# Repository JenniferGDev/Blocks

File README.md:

# Blocks
Modular Utility PCB System for breadboarding.

See the following thread where I introduced my personal breadboarding system:
https://www.modwiggler.com/forum/viewtopic.php?t=267893

The files provided here are in Kicad format.

The gerber files are available in gerber.zip.  They are setup for JLCPCB.

There is a "3D View.png" file in each module's folder, which is a screenshot of the PCB in Kicad's 3D Viewer.

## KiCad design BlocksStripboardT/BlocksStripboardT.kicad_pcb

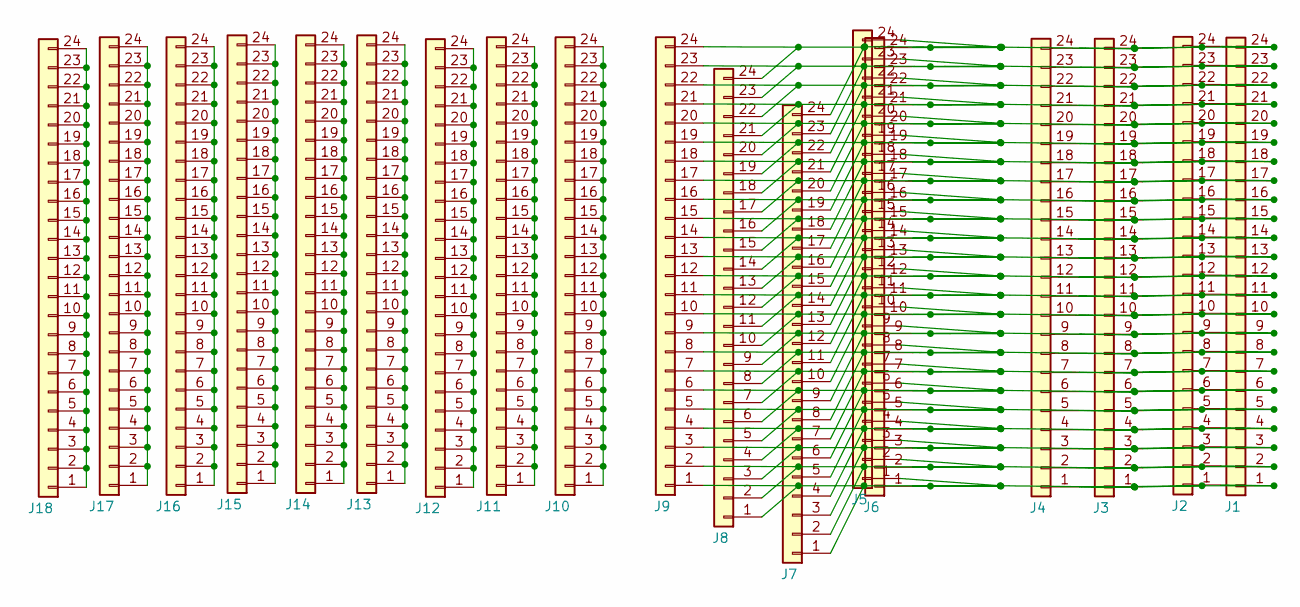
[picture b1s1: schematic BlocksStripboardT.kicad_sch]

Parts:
J1, J2, J3, J4, J5, J6, J7, J8, J9, J10, J11, J12, J13, J14, J15, J16, J17, J18: Conn_01x24; Stripboard_1x24_P2.54mm_Vertical

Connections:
unnamed: J1.1, J2.1, J3.1, J4.1, J5.1, J6.1, J7.1, J8.1, J9.1
unnamed: J1.2, J2.2, J3.2, J4.2, J5.2, J6.2, J7.2, J8.2, J9.2
unnamed: J1.3, J2.3, J3.3, J4.3, J5.3, J6.3, J7.3, J8.3, J9.3
unnamed: J1.5, J2.5, J3.5, J4.5, J5.5, J6.5, J7.5, J8.5, J9.5
unnamed: J1.4, J2.4, J3.4, J4.4, J5.4, J6.4, J7.4, J8.4, J9.4
unnamed: J1.6, J2.6, J3.6, J4.6, J5.6, J6.6, J7.6, J8.6, J9.6
unnamed: J1.7, J2.7, J3.7, J4.7, J5.7, J6.7, J7.7, J8.7, J9.7
unnamed: J1.8, J2.8, J3.8, J4.8, J5.8, J6.8, J7.8, J8.8, J9.8
unnamed: J1.9, J2.9, J3.9, J4.9, J5.9, J6.9, J7.9, J8.9, J9.9
unnamed: J1.10, J2.10, J3.10, J4.10, J5.10, J6.10, J7.10, J8.10, J9.10
unnamed: J1.11, J2.11, J3.11, J4.11, J5.11, J6.11, J7.11, J8.11, J9.11
unnamed: J1.12, J2.12, J3.12, J4.12, J5.12, J6.12, J7.12, J8.12, J9.12
unnamed: J1.13, J2.13, J3.13, J4.13, J5.13, J6.13, J7.13, J8.13, J9.13
unnamed: J1.14, J2.14, J3.14, J4.14, J5.14, J6.14, J7.14, J8.14, J9.14
unnamed: J1.15, J2.15, J3.15, J4.15, J5.15, J6.15, J7.15, J8.15, J9.15
unnamed: J1.16, J2.16, J3.16, J4.16, J5.16, J6.16, J7.16, J8.16, J9.16
unnamed: J1.17, J2.17, J3.17, J4.17, J5.17, J6.17, J7.17, J8.17, J9.17
unnamed: J1.18, J2.18, J3.18, J4.18, J5.18, J6.18, J7.18, J8.18, J9.18
unnamed: J1.19, J2.19, J3.19, J4.19, J5.19, J6.19, J7.19, J8.19, J9.19
unnamed: J1.20, J2.20, J3.20, J4.20, J5.20, J6.20, J7.20, J8.20, J9.20
unnamed: J1.21, J2.21, J3.21, J4.21, J5.21, J6.21, J7.21, J8.21, J9.21
unnamed: J1.22, J2.22, J3.22, J4.22, J5.22, J6.22, J7.22, J8.22, J9.22
unnamed: J1.23, J2.23, J3.23, J4.23, J5.23, J6.23, J7.23, J8.23, J9.23
unnamed: J1.24, J2.24, J3.24, J4.24, J5.24, J6.24, J7.24, J8.24, J9.24
unnamed: J10.1, J10.2, J10.3, J10.4, J10.5, J10.6, J10.7, J10.8, J10.9, J10.10, J10.11, J10.12, J10.13, J10.14, J10.15, J10.16, J10.17, J10.18, J10.19, J10.20, J10.21, J10.22, J10.23, J10.24
unnamed: J11.1, J11.2, J11.3, J11.4, J11.5, J11.6, J11.7, J11.8, J11.9, J11.10, J11.11, J11.12, J11.13, J11.14, J11.15, J11.16, J11.17, J11.18, J11.19, J11.20, J11.21, J11.22, J11.23, J11.24
unnamed: J12.1, J12.2, J12.3, J12.4, J12.5, J12.6, J12.7, J12.8, J12.9, J12.10, J12.11, J12.12, J12.13, J12.14, J12.15, J12.16, J12.17, J12.18, J12.19, J12.20, J12.21, J12.22, J12.23, J12.24
unnamed: J13.1, J13.2, J13.3, J13.4, J13.5, J13.6, J13.7, J13.8, J13.9, J13.10, J13.11, J13.12, J13.13, J13.14, J13.15, J13.16, J13.17, J13.18, J13.19, J13.20, J13.21, J13.22, J13.23, J13.24
unnamed: J14.1, J14.2, J14.3, J14.4, J14.5, J14.6, J14.7, J14.8, J14.9, J14.10, J14.11, J14.12, J14.13, J14.14, J14.15, J14.16, J14.17, J14.18, J14.19, J14.20, J14.21, J14.22, J14.23, J14.24
unnamed: J15.1, J15.2, J15.3, J15.4, J15.5, J15.6, J15.7, J15.8, J15.9, J15.10, J15.11, J15.12, J15.13, J15.14, J15.15, J15.16, J15.17, J15.18, J15.19, J15.20, J15.21, J15.22, J15.23, J15.24
unnamed: J16.1, J16.2, J16.3, J16.4, J16.5, J16.6, J16.7, J16.8, J16.9, J16.10, J16.11, J16.12, J16.13, J16.14, J16.15, J16.16, J16.17, J16.18, J16.19, J16.20, J16.21, J16.22, J16.23, J16.24
unnamed: J17.1, J17.2, J17.3, J17.4, J17.5, J17.6, J17.7, J17.8, J17.9, J17.10, J17.11, J17.12, J17.13, J17.14, J17.15, J17.16, J17.17, J17.18, J17.19, J17.20, J17.21, J17.22, J17.23, J17.24
unnamed: J18.1, J18.2, J18.3, J18.4, J18.5, J18.6, J18.7, J18.8, J18.9, J18.10, J18.11, J18.12, J18.13, J18.14, J18.15, J18.16, J18.17, J18.18, J18.19, J18.20, J18.21, J18.22, J18.23, J18.24

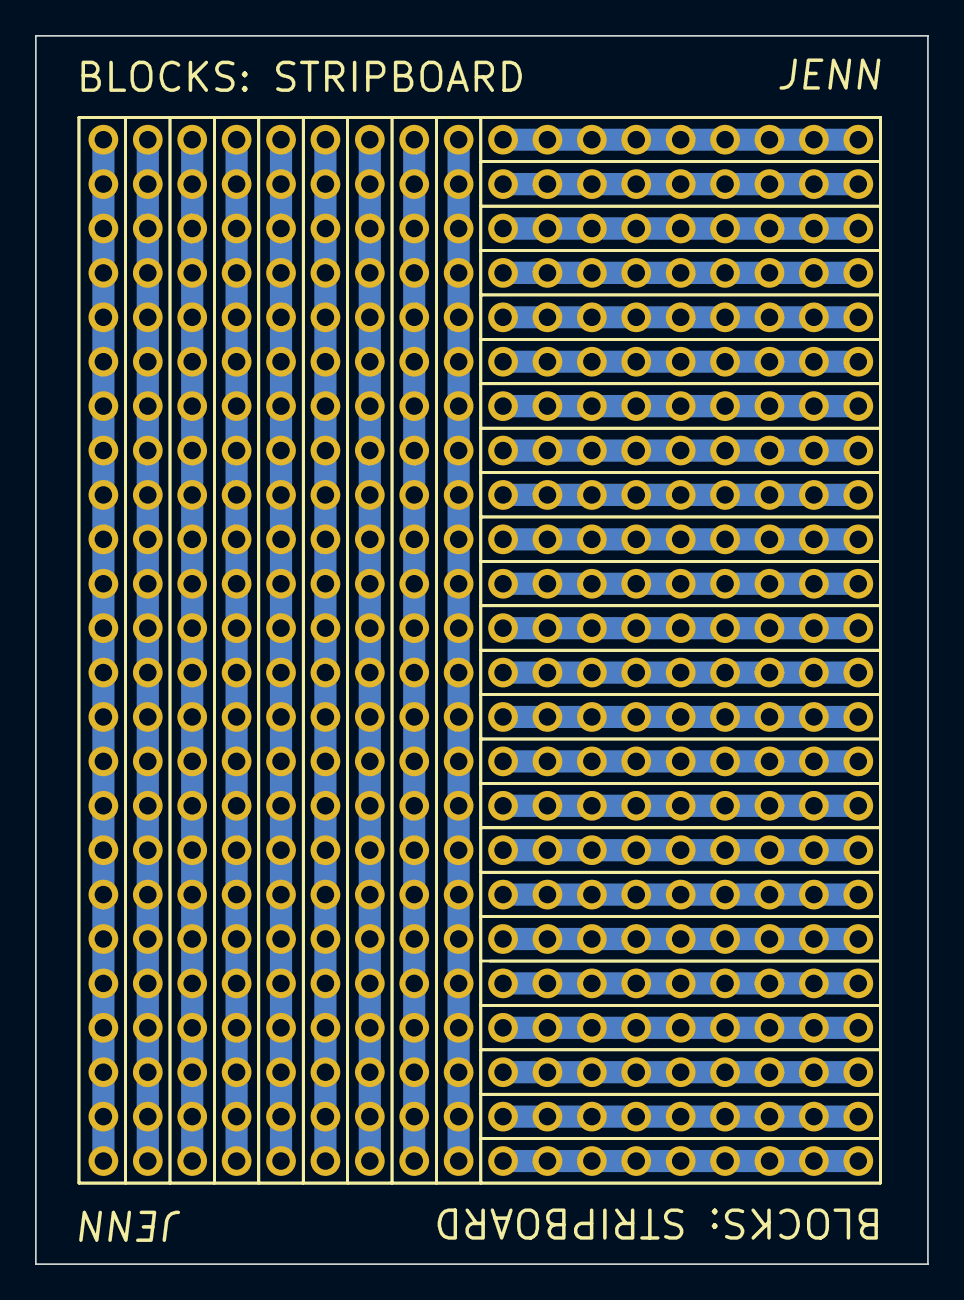
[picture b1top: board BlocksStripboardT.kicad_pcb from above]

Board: 2 copper layers, 51.0 x 70.3 mm, 18 parts (0 on the bottom side), 33 nets.

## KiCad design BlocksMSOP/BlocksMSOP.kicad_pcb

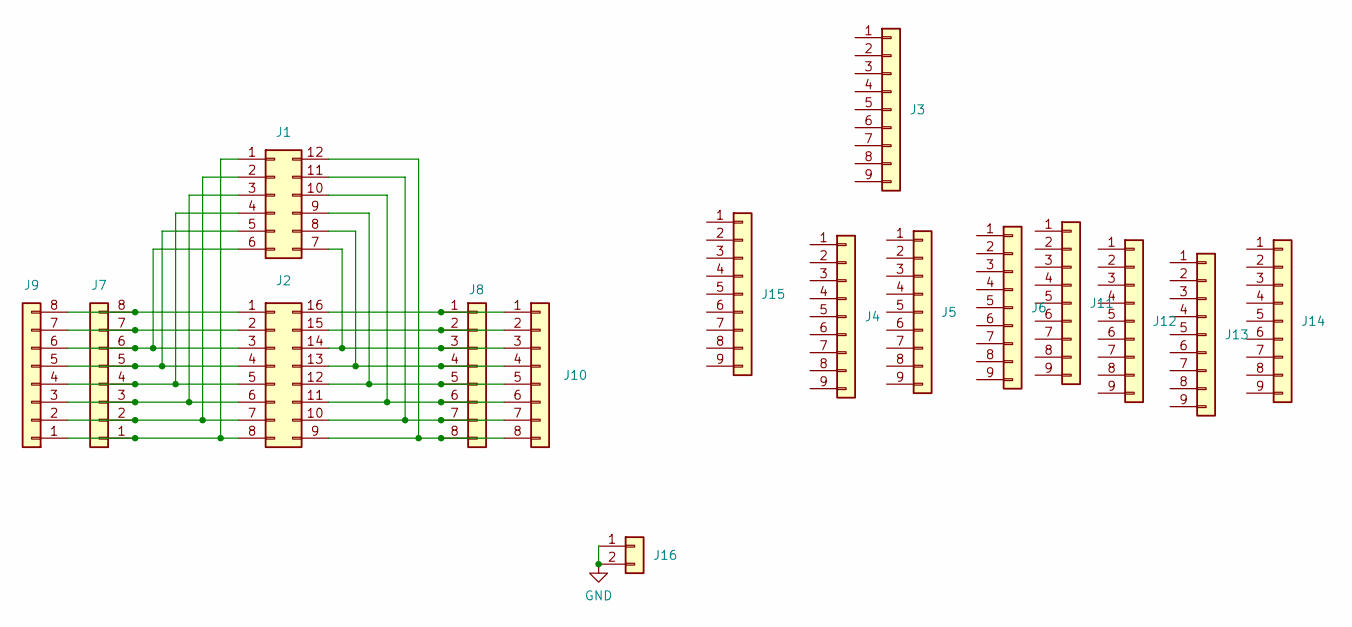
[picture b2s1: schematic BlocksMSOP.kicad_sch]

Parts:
J1: Conn_02x06_Counter_Clockwise; MSOP-12_3x4mm_P0.65mm
J2: Conn_02x08_Counter_Clockwise; MSOP-16_3x4mm_P0.5mm
J3, J4, J5, J6, J11, J12, J13, J14, J15: Conn_01x09; Stripboard_1x09_P2.54mm_Vertical
J7, J8, J9, J10: Conn_01x08; PinHeader_1x08_P2.54mm_Vertical
J16: Conn_01x02; Stripboard_1x02_P2.54mm_Vertical

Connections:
GND: J16.1, J16.2
unnamed: J1.1, J2.8, J7.1, J9.1
unnamed: J1.2, J2.7, J7.2, J9.2
unnamed: J1.3, J2.6, J7.3, J9.3
unnamed: J1.4, J2.5, J7.4, J9.4
unnamed: J1.5, J2.4, J7.5, J9.5
unnamed: J1.6, J2.3, J7.6, J9.6
unnamed: J1.7, J2.14, J8.3, J10.3
unnamed: J1.8, J2.13, J8.4, J10.4
unnamed: J1.9, J2.12, J8.5, J10.5
unnamed: J1.10, J2.11, J8.6, J10.6
unnamed: J1.11, J2.10, J8.7, J10.7
unnamed: J1.12, J2.9, J8.8, J10.8
unnamed: J2.1, J7.8, J9.8
unnamed: J2.2, J7.7, J9.7
unnamed: J2.16, J8.1, J10.1
unnamed: J2.15, J8.2, J10.2

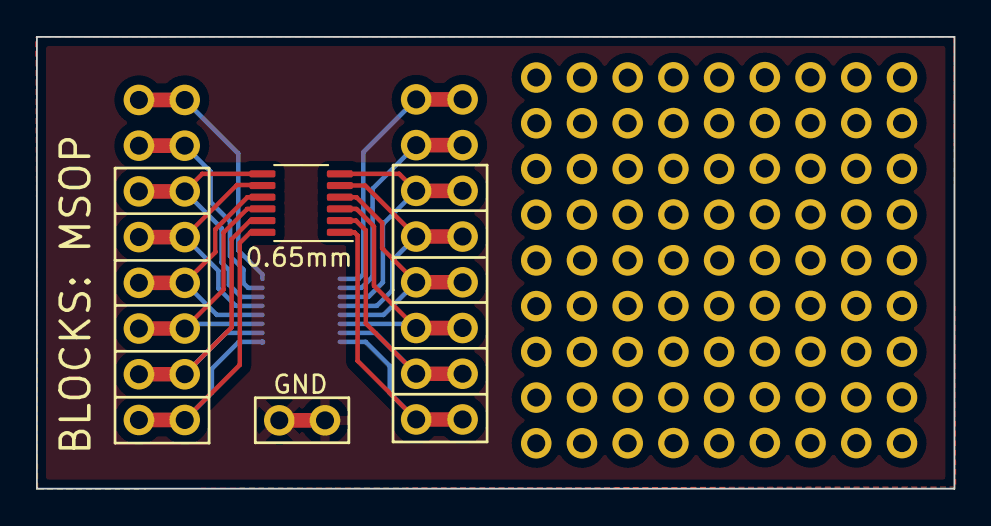
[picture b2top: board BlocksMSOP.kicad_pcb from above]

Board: 2 copper layers, 51.0 x 25.1 mm, 16 parts (1 on the bottom side), 17 nets.

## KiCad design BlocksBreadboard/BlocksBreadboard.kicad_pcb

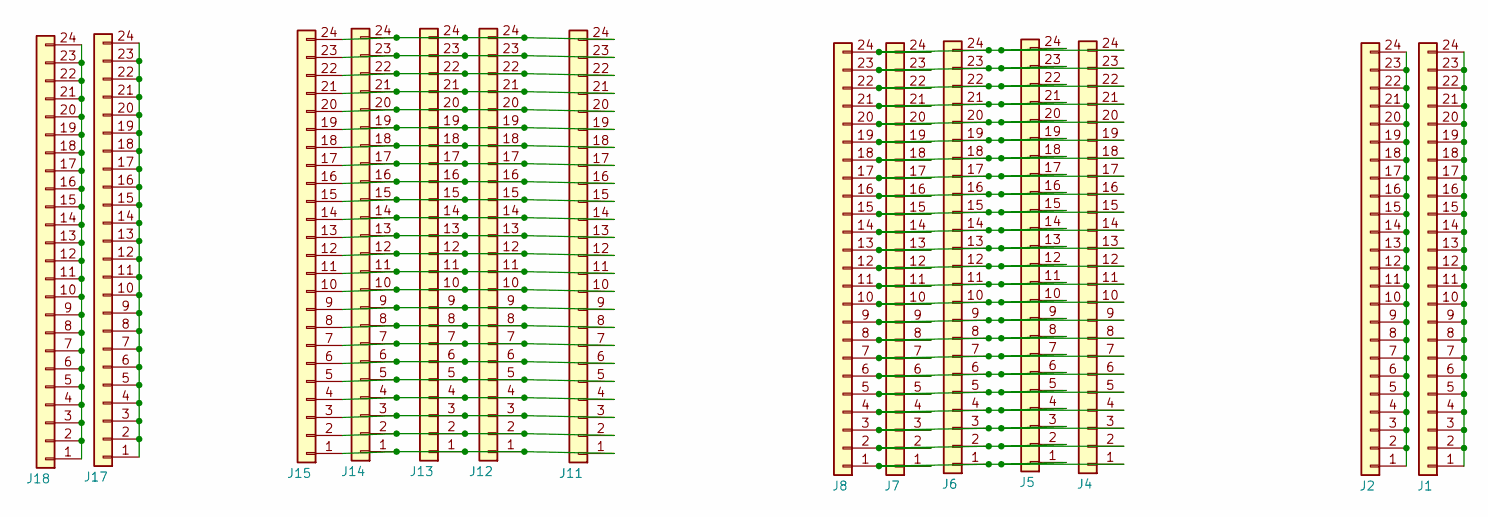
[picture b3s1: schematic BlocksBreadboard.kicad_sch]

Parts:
J1, J2, J4, J5, J6, J7, J8, J11, J12, J13, J14, J15, J17, J18: Conn_01x24; Stripboard_1x24_P2.54mm_Vertical

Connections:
unnamed: J1.1, J1.2, J1.3, J1.4, J1.5, J1.6, J1.7, J1.8, J1.9, J1.10, J1.11, J1.12, J1.13, J1.14, J1.15, J1.16, J1.17, J1.18, J1.19, J1.20, J1.21, J1.22, J1.23, J1.24
unnamed: J2.1, J2.2, J2.3, J2.4, J2.5, J2.6, J2.7, J2.8, J2.9, J2.10, J2.11, J2.12, J2.13, J2.14, J2.15, J2.16, J2.17, J2.18, J2.19, J2.20, J2.21, J2.22, J2.23, J2.24
unnamed: J4.1, J5.1, J6.1, J7.1, J8.1
unnamed: J4.2, J5.2, J6.2, J7.2, J8.2
unnamed: J4.3, J5.3, J6.3, J7.3, J8.3
unnamed: J4.4, J5.4, J6.4, J7.4, J8.4
unnamed: J4.5, J5.5, J6.5, J7.5, J8.5
unnamed: J4.6, J5.6, J6.6, J7.6, J8.6
unnamed: J4.7, J5.7, J6.7, J7.7, J8.7
unnamed: J4.8, J5.8, J6.8, J7.8, J8.8
unnamed: J4.9, J5.9, J6.9, J7.9, J8.9
unnamed: J4.10, J5.10, J6.10, J7.10, J8.10
unnamed: J4.11, J5.11, J6.11, J7.11, J8.11
unnamed: J4.12, J5.12, J6.12, J7.12, J8.12
unnamed: J4.24, J5.24, J6.24, J7.24, J8.24
unnamed: J4.13, J5.13, J6.13, J7.13, J8.13
unnamed: J4.14, J5.14, J6.14, J7.14, J8.14
unnamed: J4.15, J5.15, J6.15, J7.15, J8.15
unnamed: J4.16, J5.16, J6.16, J7.16, J8.16
unnamed: J4.17, J5.17, J6.17, J7.17, J8.17
unnamed: J4.18, J5.18, J6.18, J7.18, J8.18
unnamed: J4.19, J5.19, J6.19, J7.19, J8.19
unnamed: J4.20, J5.20, J6.20, J7.20, J8.20
unnamed: J4.21, J5.21, J6.21, J7.21, J8.21
unnamed: J4.22, J5.22, J6.22, J7.22, J8.22
unnamed: J4.23, J5.23, J6.23, J7.23, J8.23
unnamed: J11.1, J12.1, J13.1, J14.1, J15.1
unnamed: J11.2, J12.2, J13.2, J14.2, J15.2
unnamed: J11.3, J12.3, J13.3, J14.3, J15.3
unnamed: J11.4, J12.4, J13.4, J14.4, J15.4
unnamed: J11.5, J12.5, J13.5, J14.5, J15.5
unnamed: J11.6, J12.6, J13.6, J14.6, J15.6
unnamed: J11.7, J12.7, J13.7, J14.7, J15.7
unnamed: J11.8, J12.8, J13.8, J14.8, J15.8
unnamed: J11.9, J12.9, J13.9, J14.9, J15.9
unnamed: J11.10, J12.10, J13.10, J14.10, J15.10
unnamed: J11.11, J12.11, J13.11, J14.11, J15.11
unnamed: J11.12, J12.12, J13.12, J14.12, J15.12
unnamed: J11.13, J12.13, J13.13, J14.13, J15.13
unnamed: J11.14, J12.14, J13.14, J14.14, J15.14
unnamed: J11.15, J12.15, J13.15, J14.15, J15.15
unnamed: J11.16, J12.16, J13.16, J14.16, J15.16
unnamed: J11.17, J12.17, J13.17, J14.17, J15.17
unnamed: J11.18, J12.18, J13.18, J14.18, J15.18
unnamed: J11.19, J12.19, J13.19, J14.19, J15.19
unnamed: J11.20, J12.20, J13.20, J14.20, J15.20
unnamed: J11.21, J12.21, J13.21, J14.21, J15.21
unnamed: J11.22, J12.22, J13.22, J14.22, J15.22
unnamed: J11.23, J12.23, J13.23, J14.23, J15.23
unnamed: J11.24, J12.24, J13.24, J14.24, J15.24
unnamed: J17.1, J17.2, J17.3, J17.4, J17.5, J17.6, J17.7, J17.8, J17.9, J17.10, J17.11, J17.12, J17.13, J17.14, J17.15, J17.16, J17.17, J17.18, J17.19, J17.20, J17.21, J17.22, J17.23, J17.24
unnamed: J18.1, J18.2, J18.3, J18.4, J18.5, J18.6, J18.7, J18.8, J18.9, J18.10, J18.11, J18.12, J18.13, J18.14, J18.15, J18.16, J18.17, J18.18, J18.19, J18.20, J18.21, J18.22, J18.23, J18.24

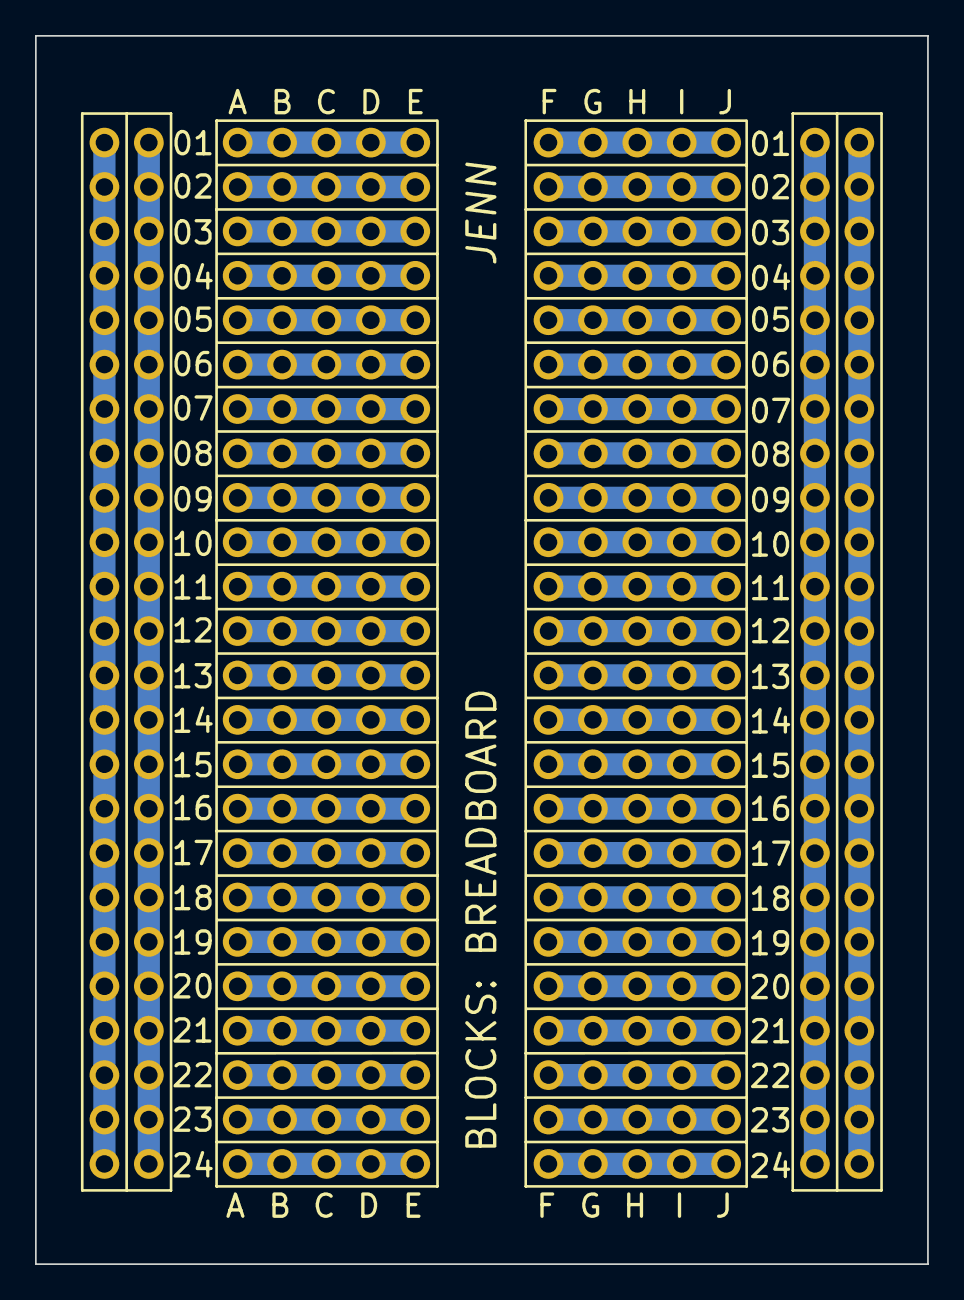
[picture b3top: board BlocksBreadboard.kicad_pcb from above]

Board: 2 copper layers, 51.0 x 70.3 mm, 14 parts (0 on the bottom side), 52 nets.

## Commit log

2022-11-18 Initial
2022-11-18 Gerber folder not needed as there is a gerber.zip
2022-11-18 Added link to forum post introducing my system
